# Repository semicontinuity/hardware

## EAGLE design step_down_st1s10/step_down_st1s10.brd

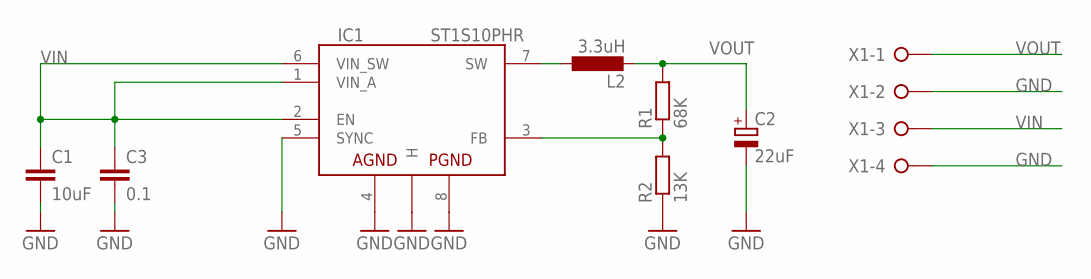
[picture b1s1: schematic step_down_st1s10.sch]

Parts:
C1: 10uF; C1210
C2: 22uF; D/7343-31R
C3: 0.1; C1210
IC1: ST1S10PHR; HSOP8
L2: 3.3uH; PIS2816
R1: 68K; R0805
R2: 13K; R0805
X1: W237-04P; W237-4P

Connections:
GND: C1.2, C2.-, C3.2, IC1.4 (AGND), IC1.5 (SYNC), IC1.8 (PGND), IC1.H@1 (H), R2.1, X1.2, X1.4
unnamed: IC1.3 (FB), R1.1, R2.2
unnamed: IC1.7 (SW), L2.1
VIN: C1.1, C3.1, IC1.1 (VIN_A), IC1.2 (EN), IC1.6 (VIN_SW), X1.3
VOUT: C2.+, L2.2, R1.2, X1.1

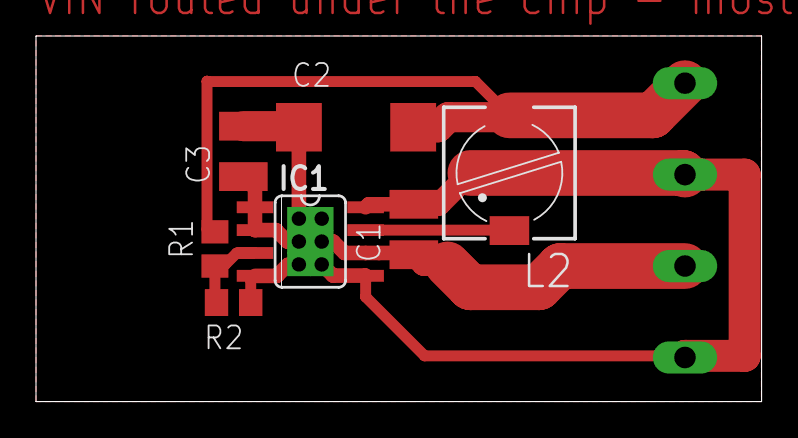
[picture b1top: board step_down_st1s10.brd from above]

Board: 2 copper layers, 40.3 x 20.3 mm, 8 parts (1 on the bottom side), 5 nets.

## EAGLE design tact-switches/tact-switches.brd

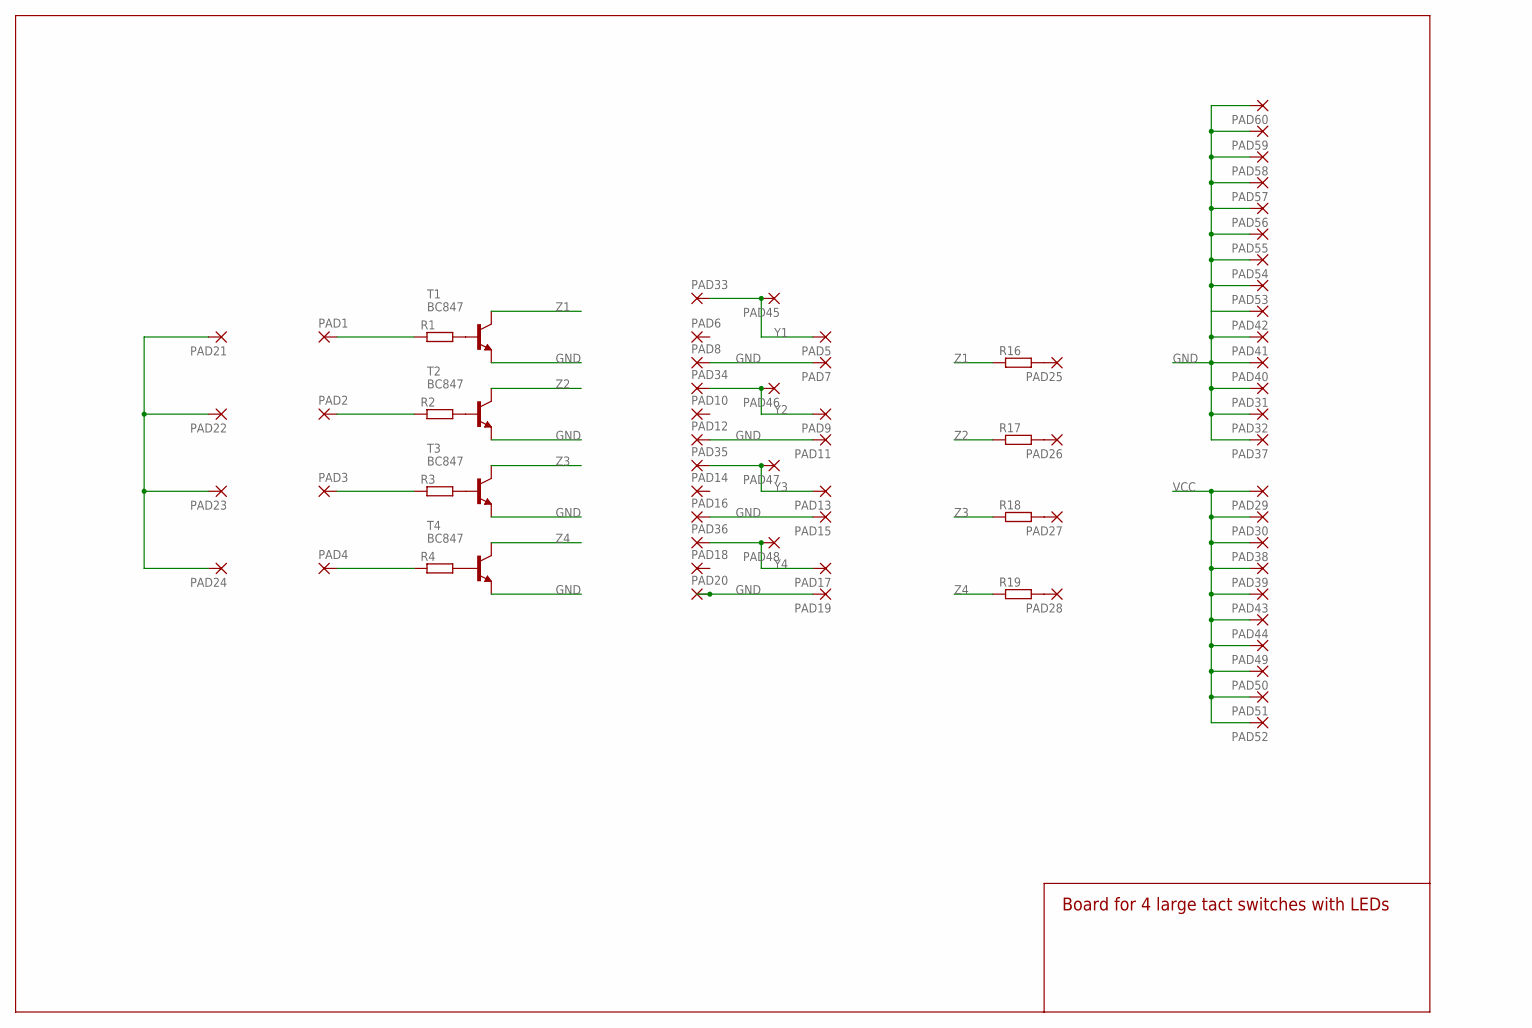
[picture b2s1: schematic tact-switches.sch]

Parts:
PAD1, PAD2, PAD3, PAD4, PAD5, PAD6, PAD7, PAD8, PAD9, PAD10, PAD11, PAD12, PAD13, PAD14, PAD15, PAD16, PAD17, PAD18, PAD19, PAD20, PAD21, PAD22, PAD23, PAD24, PAD25, PAD26, PAD27, PAD28, PAD29, PAD30, PAD31, PAD32, PAD33, PAD34, PAD35, PAD36, PAD37, PAD38, PAD39, PAD40, PAD41, PAD42, PAD43, PAD44, PAD45, PAD46, PAD47, PAD48, PAD49, PAD50, PAD51, PAD52, PAD53, PAD54, PAD55, PAD56, PAD57, PAD58, PAD59, PAD60: 1,6/0,8
R1, R2, R3, R4, R16, R17, R18, R19: R-EU_M0805; M0805
T1, T2, T3, T4: BC847; SOT23

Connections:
GND: PAD7.1, PAD8.1, PAD11.1, PAD12.1, PAD15.1, PAD16.1, PAD19.1, PAD20.1, PAD31.1, PAD32.1, PAD37.1, PAD40.1, PAD41.1, PAD42.1, PAD53.1, PAD54.1, PAD55.1, PAD56.1, PAD57.1, PAD58.1, PAD59.1, PAD60.1, T1.2 (E), T2.2 (E), T3.2 (E), T4.2 (E)
unnamed: R1.2, T1.1 (B)
unnamed: R2.2, T2.1 (B)
unnamed: R3.2, T3.1 (B)
unnamed: R4.2, T4.1 (B)
unnamed: PAD1.1, R1.1
unnamed: PAD2.1, R2.1
unnamed: PAD3.1, R3.1
unnamed: PAD4.1, R4.1
unnamed: PAD21.1, PAD22.1, PAD23.1, PAD24.1
unnamed: PAD25.1, R16.2
unnamed: PAD26.1, R17.2
unnamed: PAD27.1, R18.2
unnamed: PAD28.1, R19.2
VCC: PAD29.1, PAD30.1, PAD38.1, PAD39.1, PAD43.1, PAD44.1, PAD49.1, PAD50.1, PAD51.1, PAD52.1
Y1: PAD5.1, PAD33.1, PAD45.1
Y2: PAD9.1, PAD34.1, PAD46.1
Y3: PAD13.1, PAD35.1, PAD47.1
Y4: PAD17.1, PAD36.1, PAD48.1
Z1: R16.1, T1.3 (C)
Z2: R17.1, T2.3 (C)
Z3: R18.1, T3.3 (C)
Z4: R19.1, T4.3 (C)

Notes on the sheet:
Board for 4 large tact switches with LEDs

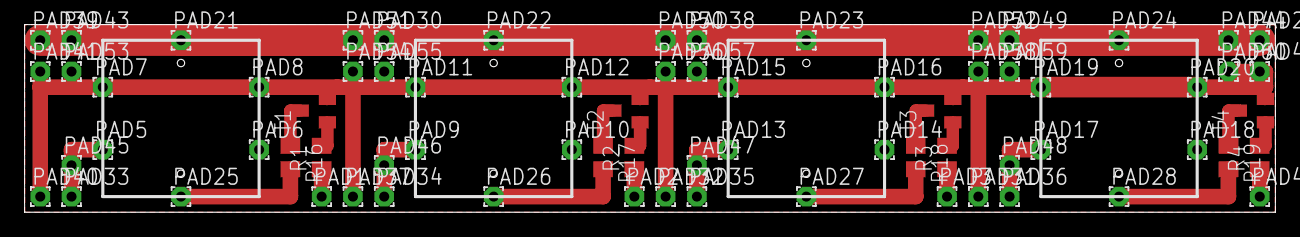
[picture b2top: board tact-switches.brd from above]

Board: 2 copper layers, 101.6 x 15.2 mm, 72 parts (0 on the bottom side), 23 nets.

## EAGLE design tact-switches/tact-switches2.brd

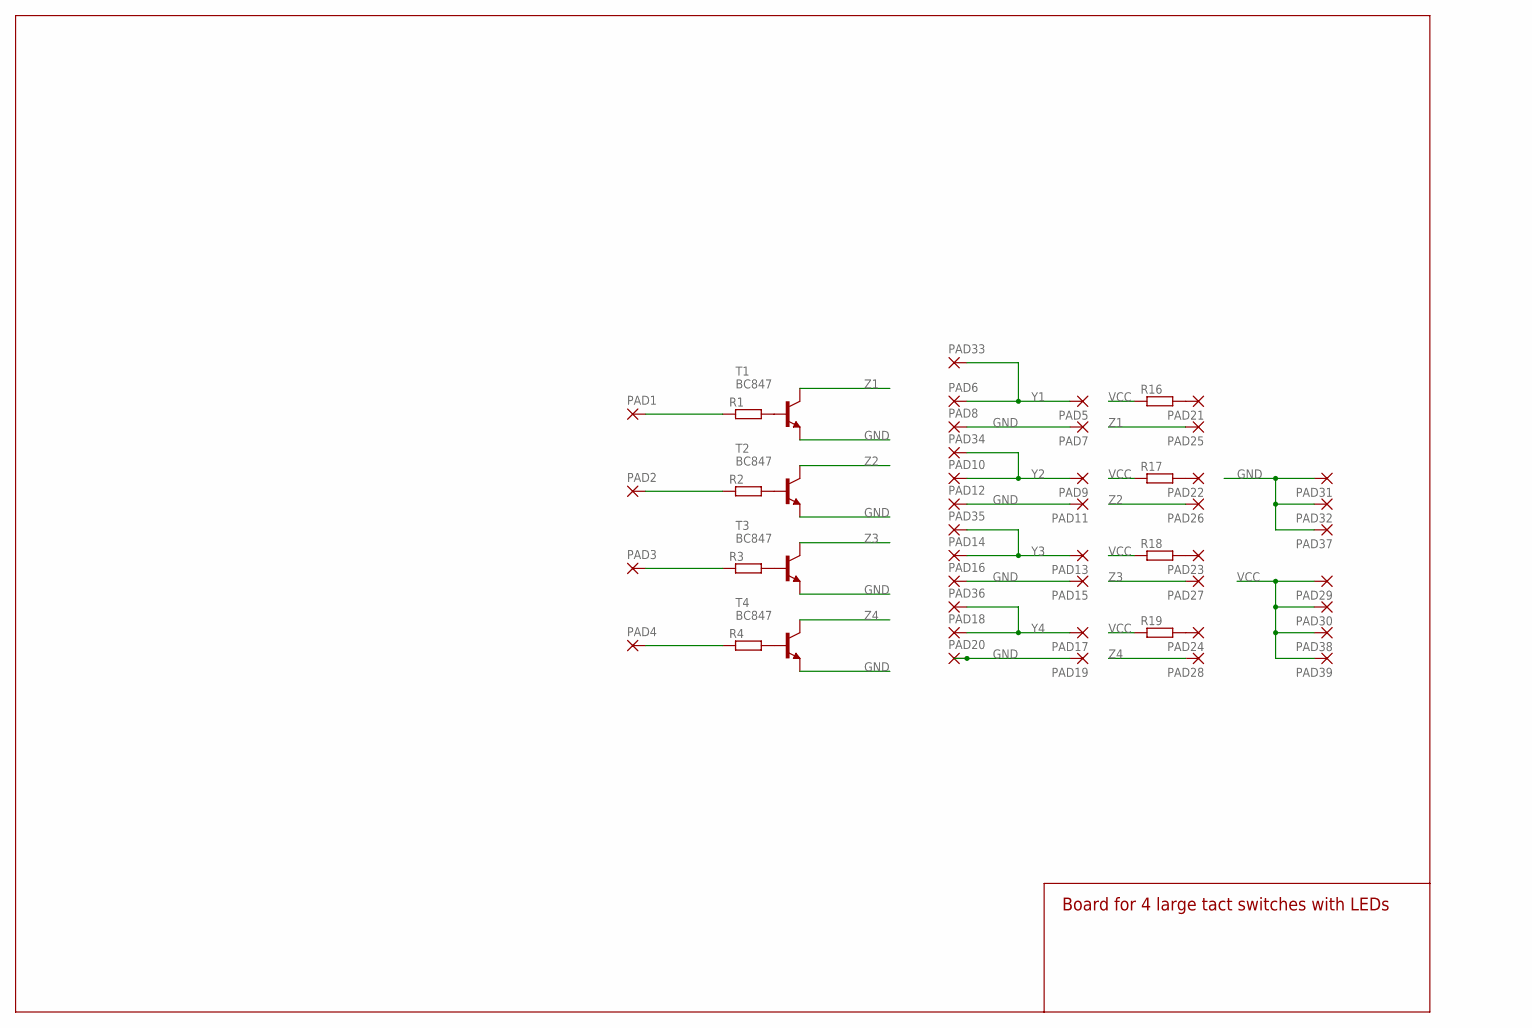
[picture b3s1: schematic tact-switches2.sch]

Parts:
PAD1, PAD2, PAD3, PAD4, PAD5, PAD6, PAD7, PAD8, PAD9, PAD10, PAD11, PAD12, PAD13, PAD14, PAD15, PAD16, PAD17, PAD18, PAD19, PAD20, PAD21, PAD22, PAD23, PAD24, PAD25, PAD26, PAD27, PAD28, PAD29, PAD30, PAD31, PAD32, PAD33, PAD34, PAD35, PAD36, PAD37, PAD38, PAD39: 1,6/0,8
R1, R2, R3, R4, R16, R17, R18, R19: R-EU_M0805; M0805
T1, T2, T3, T4: BC847; SOT23

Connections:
GND: PAD7.1, PAD8.1, PAD11.1, PAD12.1, PAD15.1, PAD16.1, PAD19.1, PAD20.1, PAD31.1, PAD32.1, PAD37.1, T1.2 (E), T2.2 (E), T3.2 (E), T4.2 (E)
unnamed: R1.2, T1.1 (B)
unnamed: R2.2, T2.1 (B)
unnamed: R3.2, T3.1 (B)
unnamed: R4.2, T4.1 (B)
unnamed: PAD1.1, R1.1
unnamed: PAD2.1, R2.1
unnamed: PAD3.1, R3.1
unnamed: PAD4.1, R4.1
unnamed: PAD21.1, R16.2
unnamed: PAD22.1, R17.2
unnamed: PAD23.1, R18.2
unnamed: PAD24.1, R19.2
VCC: PAD29.1, PAD30.1, PAD38.1, PAD39.1, R16.1, R17.1, R18.1, R19.1
Y1: PAD5.1, PAD6.1, PAD33.1
Y2: PAD9.1, PAD10.1, PAD34.1
Y3: PAD13.1, PAD14.1, PAD35.1
Y4: PAD17.1, PAD18.1, PAD36.1
Z1: PAD25.1, T1.3 (C)
Z2: PAD26.1, T2.3 (C)
Z3: PAD27.1, T3.3 (C)
Z4: PAD28.1, T4.3 (C)

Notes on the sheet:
Board for 4 large tact switches with LEDs

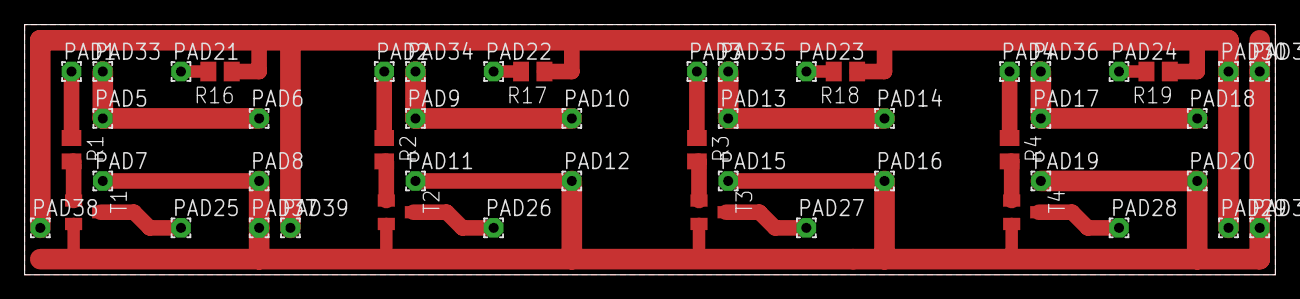
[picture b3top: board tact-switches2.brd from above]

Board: 2 copper layers, 101.6 x 20.3 mm, 51 parts (0 on the bottom side), 22 nets.

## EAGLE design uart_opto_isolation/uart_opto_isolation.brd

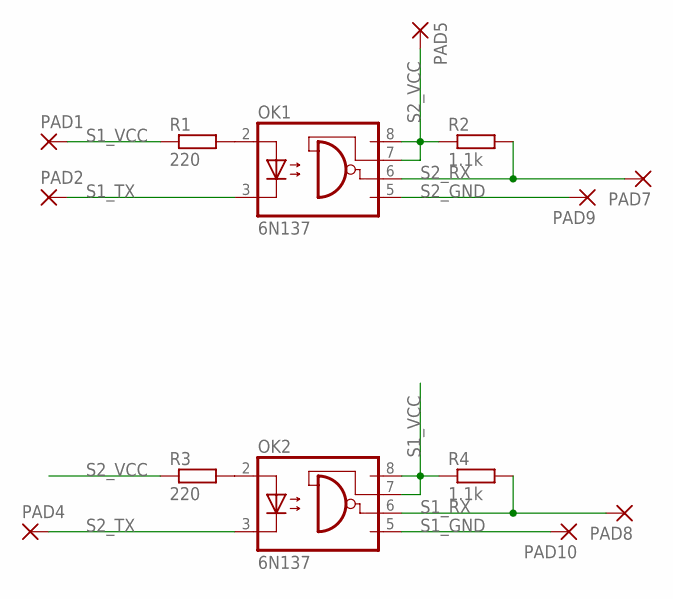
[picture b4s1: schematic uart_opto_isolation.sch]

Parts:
OK1: 6N137; DIL08
OK2: 6N137; DIL08; MPN 6N137
PAD1, PAD2, PAD4, PAD5, PAD7, PAD8, PAD9, PAD10: 1,6/0,9
R1, R3: 220; R0805
R2, R4: 1.1k; R0805

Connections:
unnamed: OK1.2 (A), R1.2
unnamed: OK2.2 (A), R3.2
S1_GND: OK2.5 (GND), PAD10.1
S1_RX: OK2.6 (VO), PAD8.1, R4.2
S1_TX: OK1.3 (C), PAD2.1
S1_VCC: OK2.7 (VE), OK2.8 (VCC), PAD1.1, R1.1, R4.1
S2_GND: OK1.5 (GND), PAD9.1
S2_RX: OK1.6 (VO), PAD7.1, R2.2
S2_TX: OK2.3 (C), PAD4.1
S2_VCC: OK1.7 (VE), OK1.8 (VCC), PAD5.1, R2.1, R3.1

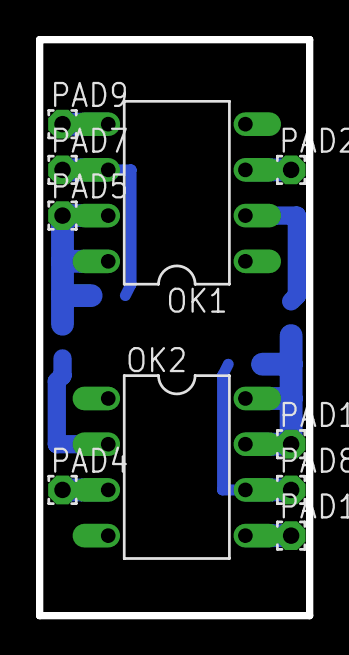
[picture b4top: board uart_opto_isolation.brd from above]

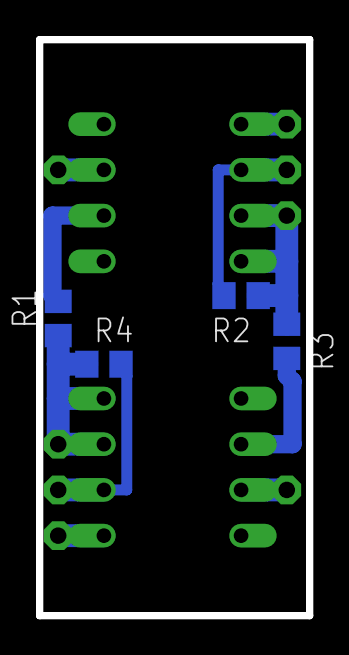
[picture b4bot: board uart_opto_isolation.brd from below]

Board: 2 copper layers, 15.0 x 32.0 mm, 14 parts (4 on the bottom side), 10 nets.

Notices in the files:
parts and their libraries:
vreg-pulse: 2009 Draw by Ivan A-R. License CC-BY-SA 3.0
